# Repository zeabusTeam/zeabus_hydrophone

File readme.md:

## README
This is the version 3 of Zeabus hydrophone system. The system is built around
an FPGA. The system takes the input from 4 hydrophones and performs signal 
conditioning and filtering before sending the outputs to the host computer via 
a USB high-speed connection. The basic specifications of the system are:
- Maximum input frequency is 45 kHz
- Minimum ADC sampling rate is 4.5 mega-sample per second (MSPS)
- Each sample has at least 14-bit resolution
- Utilizes "averaging" sampling mode to down-sampling to the appropriate rate
- Supports variable gain in pre-amplifier unit
- Maximum ADC input voltage is 2 Vp-p
- Supports variable trigger voltage.
- At least 32k samples/channel buffer length
- Perform online FIR filter with user-provided FIR table.
  - FIR filter is an odd-symetric filter (i.e., type1 linear-phase FIR)
  - Each coefficient is 2'complement 32-bit integer

## Concrete specification
ADC: AD9248BSTZ-65 (65 MSPS max)
FPGA: Xilinx Artix 7 XC7A15T (ZTEX FPGA v2.14a)
Clock Buffer: IDT-553S (1:4 Distribute)
OP-AMP: OPA2365 (Dual Op-Amp), OPA365 (Single Op-Amp) [May use -Q1 version for thougher devices]
Digital Potentiometer: MAX5413 (10k), MAX5414 (50k), MAX5415 (100k) (May use MAX5387 as alternative)
ADC Driver: ADA4940-2 to convert single-ended signal to differential signal (Transformer is unsuitable for low freq.)
Voltage Reference: REF1933 (+3.3v and +1.65v outputs are used only for reference. The device requires 5v input)
Capacitors along the signal path should be of C0G type.

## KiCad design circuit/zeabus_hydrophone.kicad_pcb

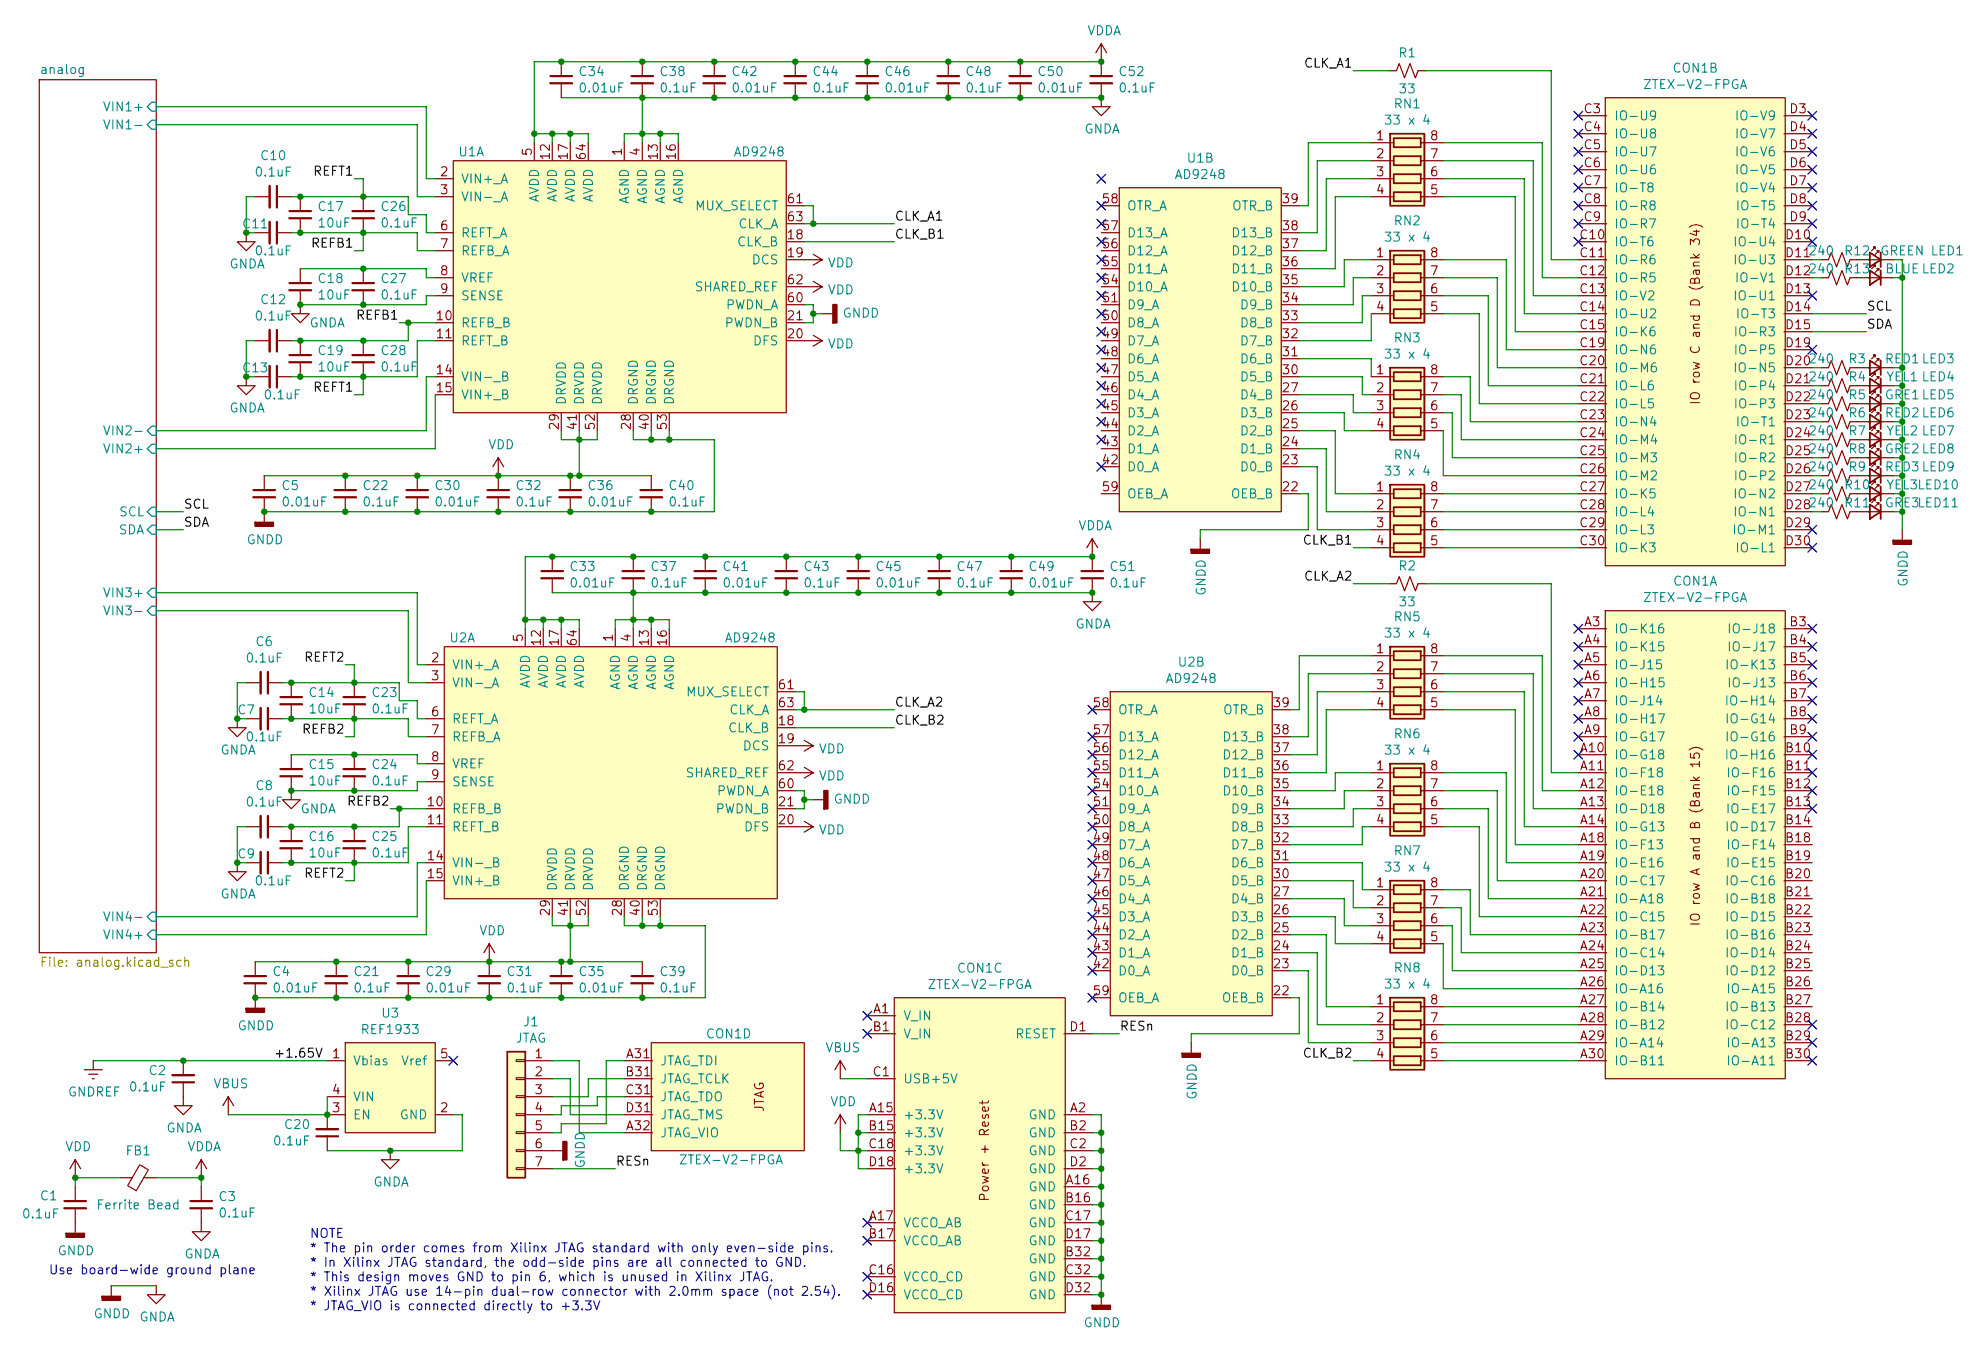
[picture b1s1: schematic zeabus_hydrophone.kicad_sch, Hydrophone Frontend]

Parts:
C1, C2, C3, C6, C7, C8, C9, C10, C11, C12, C13, C20, C21, C22, C23, C24, C25, C26, C27, C28, C31, C32, C37, C38, C39, C40, C43, C44, C47, C48, C51, C52: 0.1uF; C_0603_1608Metric_Pad1.08x0.95mm_HandSolder
C4, C5, C29, C30, C33, C34, C35, C36, C41, C42, C45, C46, C49, C50: 0.01uF; C_0603_1608Metric_Pad1.08x0.95mm_HandSolder
C14, C15, C16, C17, C18, C19: 10uF; C_0805_2012Metric_Pad1.18x1.45mm_HandSolder
CON1: ZTEX-V2-FPGA; ZTEX-V2-FPGA-SMD
FB1: Ferrite Bead; R_0805_2012Metric_Pad1.15x1.40mm_HandSolder
J1: JTAG; PinHeader_1x07_P2.54mm_Vertical
LED1: GREEN; LED_0603_1608Metric_Pad1.05x0.95mm_HandSolder
LED2: BLUE; LED_0603_1608Metric_Pad1.05x0.95mm_HandSolder
LED3: RED1; LED_0603_1608Metric_Pad1.05x0.95mm_HandSolder
LED4: YEL1; LED_0603_1608Metric_Pad1.05x0.95mm_HandSolder
LED5: GRE1; LED_0603_1608Metric_Pad1.05x0.95mm_HandSolder
LED6: RED2; LED_0603_1608Metric_Pad1.05x0.95mm_HandSolder
LED7: YEL2; LED_0603_1608Metric_Pad1.05x0.95mm_HandSolder
LED8: GRE2; LED_0603_1608Metric_Pad1.05x0.95mm_HandSolder
LED9: RED3; LED_0603_1608Metric_Pad1.05x0.95mm_HandSolder
LED10: YEL3; LED_0603_1608Metric_Pad1.05x0.95mm_HandSolder
LED11: GRE3; LED_0603_1608Metric_Pad1.05x0.95mm_HandSolder
R1, R2: 33; R_0603_1608Metric_Pad1.05x0.95mm_HandSolder
R3, R4, R5, R6, R7, R8, R9, R10, R11, R12, R13: 240; R_0603_1608Metric_Pad1.05x0.95mm_HandSolder
RN1, RN2, RN3, RN4, RN5, RN6, RN7, RN8: 33 x 4; R_Array_Convex_4x0603
U1, U2: AD9248; TQFP-64_7x7mm_P0.4mm
U3: REF1933; SOT-23-5

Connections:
/CLK_A1: R1.2, U1.61 (MUX_SELECT), U1.63 (CLK_A)
/CLK_A2: R2.2, U2.61 (MUX_SELECT), U2.63 (CLK_A)
/CLK_B1: RN4.4 (R4.1), U1.18 (CLK_B)
/CLK_B2: RN8.4 (R4.1), U2.18 (CLK_B)
/REFB1: C11.1, C12.1, C17.2, C19.1, C26.2, C28.1, U1.7 (REFB_A), U1.10 (REFB_B)
/REFB2: C7.1, C8.1, C14.2, C16.1, C23.2, C25.1, U2.7 (REFB_A), U2.10 (REFB_B)
/REFT1: C10.1, C13.1, C17.1, C19.2, C26.1, C28.2, U1.6 (REFT_A), U1.11 (REFT_B)
/REFT2: C6.1, C9.1, C14.1, C16.2, C23.1, C25.2, U2.6 (REFT_A), U2.11 (REFT_B)
/RESn: CON1.D1 (RESET), J1.7
/SCL: CON1.D14 (IO-T3); also elsewhere on the board
/SDA: CON1.D15 (IO-R3); also elsewhere on the board
/analog/VIN1+: U1.2 (VIN+_A); also elsewhere on the board
/analog/VIN1-: U1.3 (VIN-_A); also elsewhere on the board
/analog/VIN2+: U1.15 (VIN+_B); also elsewhere on the board
/analog/VIN2-: U1.14 (VIN-_B); also elsewhere on the board
/analog/VIN3+: U2.2 (VIN+_A); also elsewhere on the board
/analog/VIN3-: U2.3 (VIN-_A); also elsewhere on the board
/analog/VIN4+: U2.15 (VIN+_B); also elsewhere on the board
/analog/VIN4-: U2.14 (VIN-_B); also elsewhere on the board
GNDA: C1.2, C2.1, C3.2, C4.2, C5.2, C6.2, C7.2, C8.2, C9.2, C10.2, C11.2, C12.2, C13.2, C15.2, C18.2, C20.1, C21.2, C22.2, C24.2, C27.2, C29.2, C30.2, C31.2, C32.2, C33.2, C34.2, C35.2, C36.2, C37.2, C38.2, C39.2, C40.2, C41.2, C42.2, C43.2, C44.2, C45.2, C46.2, C47.2, C48.2, C49.2, C50.2, C51.2, C52.2, CON1.A2 (GND), CON1.A16 (GND), CON1.B2 (GND), CON1.B16 (GND), CON1.B32 (GND), CON1.C2 (GND), CON1.C17 (GND), CON1.C32 (GND), CON1.D2 (GND), CON1.D17 (GND), CON1.D32 (GND), J1.6, LED1.1 (K), LED2.1 (K), LED3.1 (K), LED4.1 (K), LED5.1 (K), LED6.1 (K), LED7.1 (K), LED8.1 (K), LED9.1 (K), LED10.1 (K), LED11.1 (K), U1.1 (AGND), U1.4 (AGND), U1.9 (SENSE), U1.13 (AGND), U1.16 (AGND), U1.21 (PWDN_B), U1.22 (OEB_B), U1.28 (DRGND), U1.40 (DRGND), U1.53 (DRGND), U1.60 (PWDN_A), U2.1 (AGND), U2.4 (AGND), U2.9 (SENSE), U2.13 (AGND), U2.16 (AGND), U2.21 (PWDN_B), U2.22 (OEB_B), U2.28 (DRGND), U2.40 (DRGND), U2.53 (DRGND), U2.60 (PWDN_A), U3.2 (GND); also elsewhere on the board
GNDREF: C2.2, U3.1 (Vbias); also elsewhere on the board
unnamed: C15.1, C24.1, U2.8 (VREF)
unnamed: C18.1, C27.1, U1.8 (VREF)
unnamed: CON1.A11 (IO-F18), R2.1
unnamed: CON1.A12 (IO-E18), RN5.8 (R1.2)
unnamed: CON1.A13 (IO-D18), RN5.7 (R2.2)
unnamed: CON1.A14 (IO-G13), RN5.6 (R3.2)
unnamed: CON1.A18 (IO-F13), RN5.5 (R4.2)
unnamed: CON1.A19 (IO-E16), RN6.8 (R1.2)
unnamed: CON1.A20 (IO-C17), RN6.7 (R2.2)
unnamed: CON1.A21 (IO-A18), RN6.6 (R3.2)
unnamed: CON1.A22 (IO-C15), RN6.5 (R4.2)
unnamed: CON1.A23 (IO-B17), RN7.8 (R1.2)
unnamed: CON1.A24 (IO-C14), RN7.7 (R2.2)
unnamed: CON1.A25 (IO-D13), RN7.6 (R3.2)
unnamed: CON1.A26 (IO-A16), RN7.5 (R4.2)
unnamed: CON1.A27 (IO-B14), RN8.8 (R1.2)
unnamed: CON1.A28 (IO-B12), RN8.7 (R2.2)
unnamed: CON1.A29 (IO-A14), RN8.6 (R3.2)
unnamed: CON1.A30 (IO-B11), RN8.5 (R4.2)
unnamed: CON1.A31 (JTAG_TDI), J1.5
unnamed: CON1.A32 (JTAG_VIO), J1.1
unnamed: CON1.B31 (JTAG_TCLK), J1.3
unnamed: CON1.C11 (IO-R6), R1.1
unnamed: CON1.C12 (IO-R5), RN1.8 (R1.2)
unnamed: CON1.C13 (IO-V2), RN1.7 (R2.2)
unnamed: CON1.C14 (IO-U2), RN1.6 (R3.2)
unnamed: CON1.C15 (IO-K6), RN1.5 (R4.2)
unnamed: CON1.C19 (IO-N6), RN2.8 (R1.2)
unnamed: CON1.C20 (IO-M6), RN2.7 (R2.2)
unnamed: CON1.C21 (IO-L6), RN2.6 (R3.2)
unnamed: CON1.C22 (IO-L5), RN2.5 (R4.2)
unnamed: CON1.C23 (IO-N4), RN3.8 (R1.2)
unnamed: CON1.C24 (IO-M4), RN3.7 (R2.2)
unnamed: CON1.C25 (IO-M3), RN3.6 (R3.2)
unnamed: CON1.C26 (IO-M2), RN3.5 (R4.2)
unnamed: CON1.C27 (IO-K5), RN4.8 (R1.2)
unnamed: CON1.C28 (IO-L4), RN4.7 (R2.2)
unnamed: CON1.C29 (IO-L3), RN4.6 (R3.2)
unnamed: CON1.C30 (IO-K3), RN4.5 (R4.2)
unnamed: CON1.C31 (JTAG_TDO), J1.4
unnamed: CON1.D11 (IO-U3), R12.1
unnamed: CON1.D12 (IO-V1), R13.1
unnamed: CON1.D20 (IO-N5), R3.2
unnamed: CON1.D21 (IO-P4), R4.2
unnamed: CON1.D22 (IO-P3), R5.2
unnamed: CON1.D23 (IO-T1), R6.2
unnamed: CON1.D24 (IO-R1), R7.2
unnamed: CON1.D25 (IO-R2), R8.2
unnamed: CON1.D26 (IO-P2), R9.2
unnamed: CON1.D27 (IO-N2), R10.2
unnamed: CON1.D28 (IO-N1), R11.2
unnamed: CON1.D31 (JTAG_TMS), J1.2
unnamed: LED1.2 (A), R12.2
unnamed: LED2.2 (A), R13.2
unnamed: LED3.2 (A), R3.1
unnamed: LED4.2 (A), R4.1
unnamed: LED5.2 (A), R5.1
unnamed: LED6.2 (A), R6.1
unnamed: LED7.2 (A), R7.1
unnamed: LED8.2 (A), R8.1
unnamed: LED9.2 (A), R9.1
unnamed: LED10.2 (A), R10.1
unnamed: LED11.2 (A), R11.1
unnamed: RN1.1 (R1.1), U1.39 (OTR_B)
unnamed: RN1.2 (R2.1), U1.38 (D13_B)
unnamed: RN1.3 (R3.1), U1.37 (D12_B)
unnamed: RN1.4 (R4.1), U1.36 (D11_B)
unnamed: RN2.1 (R1.1), U1.35 (D10_B)
unnamed: RN2.2 (R2.1), U1.34 (D9_B)
unnamed: RN2.3 (R3.1), U1.33 (D8_B)
unnamed: RN2.4 (R4.1), U1.32 (D7_B)
unnamed: RN3.1 (R1.1), U1.31 (D6_B)
unnamed: RN3.2 (R2.1), U1.30 (D5_B)
unnamed: RN3.3 (R3.1), U1.27 (D4_B)
unnamed: RN3.4 (R4.1), U1.26 (D3_B)
unnamed: RN4.1 (R1.1), U1.25 (D2_B)
unnamed: RN4.2 (R2.1), U1.24 (D1_B)
unnamed: RN4.3 (R3.1), U1.23 (D0_B)
unnamed: RN5.1 (R1.1), U2.39 (OTR_B)
unnamed: RN5.2 (R2.1), U2.38 (D13_B)
unnamed: RN5.3 (R3.1), U2.37 (D12_B)
unnamed: RN5.4 (R4.1), U2.36 (D11_B)
unnamed: RN6.1 (R1.1), U2.35 (D10_B)
unnamed: RN6.2 (R2.1), U2.34 (D9_B)
unnamed: RN6.3 (R3.1), U2.33 (D8_B)
unnamed: RN6.4 (R4.1), U2.32 (D7_B)
unnamed: RN7.1 (R1.1), U2.31 (D6_B)
unnamed: RN7.2 (R2.1), U2.30 (D5_B)
unnamed: RN7.3 (R3.1), U2.27 (D4_B)
unnamed: RN7.4 (R4.1), U2.26 (D3_B)
unnamed: RN8.1 (R1.1), U2.25 (D2_B)
unnamed: RN8.2 (R2.1), U2.24 (D1_B)
unnamed: RN8.3 (R3.1), U2.23 (D0_B)
VBUS: C20.2, CON1.C1 (USB+5V), U3.3 (EN), U3.4 (VIN)
VDD: C1.1, C4.1, C5.1, C21.1, C22.1, C29.1, C30.1, C31.1, C32.1, C35.1, C36.1, C39.1, C40.1, CON1.A15 (+3.3V), CON1.B15 (+3.3V), CON1.C18 (+3.3V), CON1.D18 (+3.3V), FB1.1, U1.19 (DCS), U1.20 (DFS), U1.29 (DRVDD), U1.41 (DRVDD), U1.52 (DRVDD), U1.62 (SHARED_REF), U2.19 (DCS), U2.20 (DFS), U2.29 (DRVDD), U2.41 (DRVDD), U2.52 (DRVDD), U2.62 (SHARED_REF); also elsewhere on the board
VDDA: C3.1, C33.1, C34.1, C37.1, C38.1, C41.1, C42.1, C43.1, C44.1, C45.1, C46.1, C47.1, C48.1, C49.1, C50.1, C51.1, C52.1, FB1.2, U1.5 (AVDD), U1.12 (AVDD), U1.17 (AVDD), U1.64 (AVDD), U2.5 (AVDD), U2.12 (AVDD), U2.17 (AVDD), U2.64 (AVDD); also elsewhere on the board

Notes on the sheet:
Use board-wide ground plane
NOTE * The pin order comes from Xilinx JTAG standard with only even-side pins. * In Xilinx JTAG standard, the odd-side pins are all connected to GND. * This design moves GND to pin 6, which is unused in Xilinx JTAG. * Xilinx JTAG use 14-pin dual-row connector with 2.0mm space (not 2.54). * JTAG_VIO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

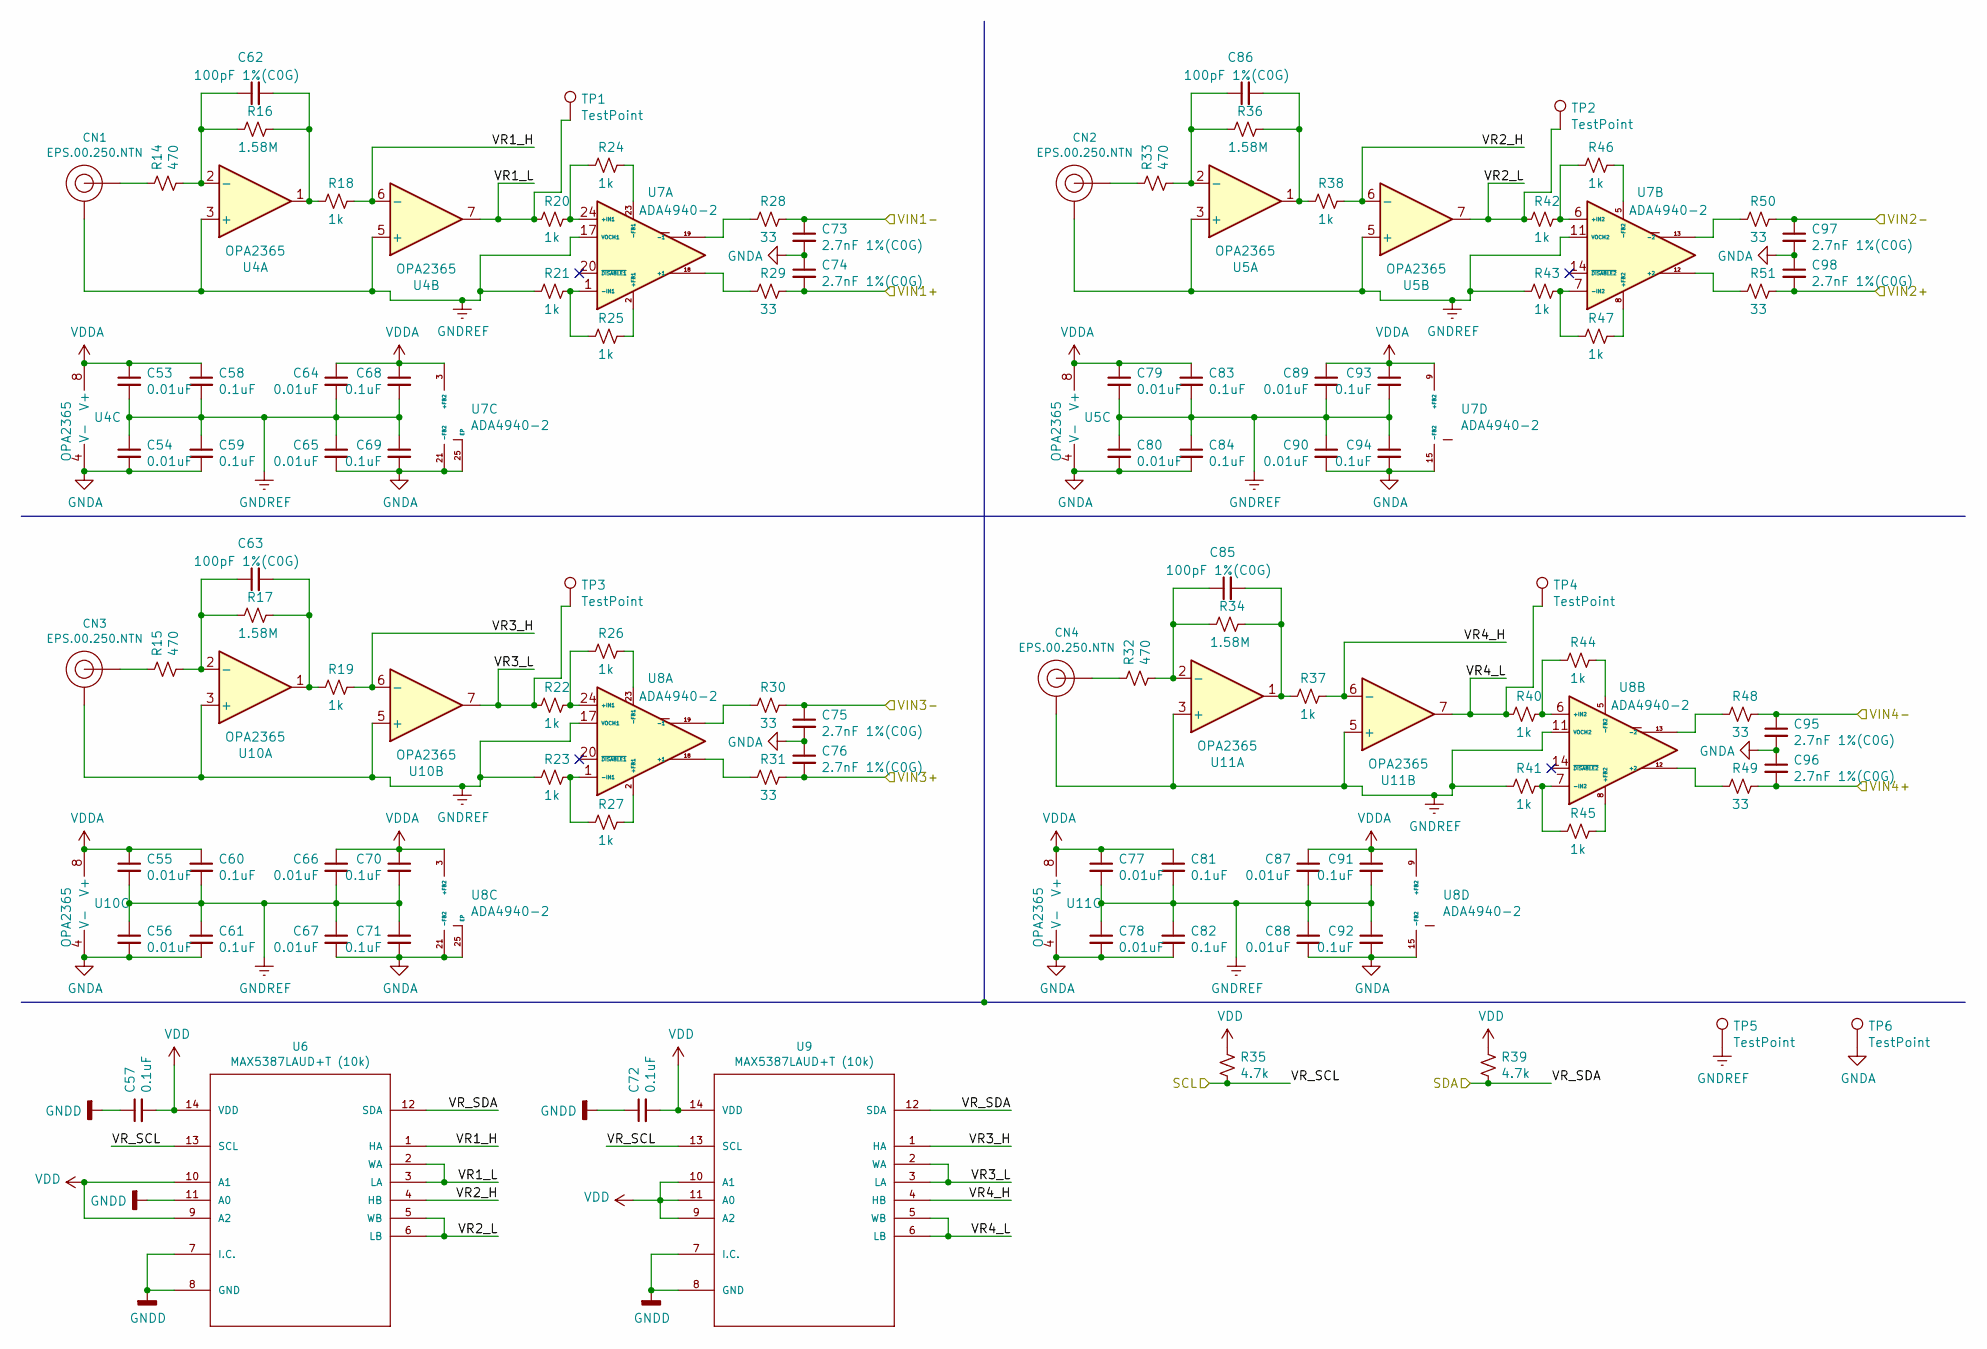
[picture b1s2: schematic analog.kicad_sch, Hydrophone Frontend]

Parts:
C53, C54, C55, C56, C64, C65, C66, C67, C77, C78, C79, C80, C87, C88, C89, C90: 0.01uF; C_0603_1608Metric_Pad1.08x0.95mm_HandSolder
C57, C58, C59, C60, C61, C68, C69, C70, C71, C72, C81, C82, C83, C84, C91, C92, C93, C94: 0.1uF; C_0603_1608Metric_Pad1.08x0.95mm_HandSolder
C62, C63, C85, C86: 100pF 1%(C0G); C_0603_1608Metric_Pad1.08x0.95mm_HandSolder
C73, C74, C75, C76, C95, C96, C97, C98: 2.7nF 1%(C0G); C_0603_1608Metric_Pad1.08x0.95mm_HandSolder
CN1, CN2, CN3, CN4: EPS.00.250.NTN; EPS-00-250
R14, R15, R32, R33: 470; R_0603_1608Metric_Pad1.05x0.95mm_HandSolder
R16, R17, R34, R36: 1.58M; R_0603_1608Metric_Pad1.05x0.95mm_HandSolder
R18, R19, R20, R21, R22, R23, R24, R25, R26, R27, R37, R38, R40, R41, R42, R43, R44, R45, R46, R47: 1k; R_0603_1608Metric_Pad1.05x0.95mm_HandSolder
R28, R29, R30, R31, R48, R49, R50, R51: 33; R_0603_1608Metric_Pad1.05x0.95mm_HandSolder
R35, R39: 4.7k; R_0603_1608Metric_Pad1.05x0.95mm_HandSolder
TP1, TP2, TP3, TP4, TP5, TP6: TestPoint; PinSocket_1x01_P2.54mm_Vertical
U4, U5, U10, U11: OPA2365; SOIC-8_3.9x4.9mm_P1.27mm
U6, U9: MAX5387LAUD+T (10k); TSSOP-14_4.4x5mm_P0.65mm
U7, U8: ADA4940-2; LFCSP-24-1EP_4x4mm_P0.5mm_EP2.5x2.5mm

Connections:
/SCL: R35.2, U6.13 (SCL), U9.13 (SCL); also elsewhere on the board
/SDA: R39.2, U6.12 (SDA), U9.12 (SDA); also elsewhere on the board
/analog/VIN1+: C74.2, R29.1; also elsewhere on the board
/analog/VIN1-: C73.1, R28.1; also elsewhere on the board
/analog/VIN2+: C98.2, R51.1; also elsewhere on the board
/analog/VIN2-: C97.1, R50.1; also elsewhere on the board
/analog/VIN3+: C76.2, R31.1; also elsewhere on the board
/analog/VIN3-: C75.1, R30.1; also elsewhere on the board
/analog/VIN4+: C96.2, R49.1; also elsewhere on the board
/analog/VIN4-: C95.1, R48.1; also elsewhere on the board
/analog/VR1_H: R18.1, U4.6 (-), U6.1 (HA)
/analog/VR1_L: R20.2, TP1.1, U4.7, U6.2 (WA), U6.3 (LA)
/analog/VR2_H: R38.1, U5.6 (-), U6.4 (HB)
/analog/VR2_L: R42.2, TP2.1, U5.7, U6.5 (WB), U6.6 (LB)
/analog/VR3_H: R19.1, U9.1 (HA), U10.6 (-)
/analog/VR3_L: R22.2, TP3.1, U9.2 (WA), U9.3 (LA), U10.7
/analog/VR4_H: R37.1, U9.4 (HB), U11.6 (-)
/analog/VR4_L: R40.2, TP4.1, U9.5 (WB), U9.6 (LB), U11.7
GNDA: C54.2, C56.2, C57.1, C59.2, C61.2, C65.2, C67.2, C69.2, C71.2, C72.1, C73.2, C74.1, C75.2, C76.1, C78.2, C80.2, C82.2, C84.2, C88.2, C90.2, C92.2, C94.2, C95.2, C96.1, C97.2, C98.1, TP6.1, U4.4 (V-), U5.4 (V-), U6.7 (I.C.), U6.8 (GND), U6.11 (A0), U7.15 (-FB2), U7.16 (-FB2), U7.21 (-FB2), U7.22 (-FB2), U7.25 (EP), U8.15 (-FB2), U8.16 (-FB2), U8.21 (-FB2), U8.22 (-FB2), U8.25 (EP), U9.7 (I.C.), U9.8 (GND), U10.4 (V-), U11.4 (V-); also elsewhere on the board
GNDREF: C53.2, C54.1, C55.2, C56.1, C58.2, C59.1, C60.2, C61.1, C64.2, C65.1, C66.2, C67.1, C68.2, C69.1, C70.2, C71.1, C77.2, C78.1, C79.2, C80.1, C81.2, C82.1, C83.2, C84.1, C87.2, C88.1, C89.2, C90.1, C91.2, C92.1, C93.2, C94.1, CN1.2 (GND), CN1.3 (GND), CN1.4 (GND), CN1.5 (GND), CN2.2 (GND), CN2.3 (GND), CN2.4 (GND), CN2.5 (GND), CN3.2 (GND), CN3.3 (GND), CN3.4 (GND), CN3.5 (GND), CN4.2 (GND), CN4.3 (GND), CN4.4 (GND), CN4.5 (GND), R21.2, R23.2, R41.2, R43.2, TP5.1, U4.3 (+), U4.5 (+), U5.3 (+), U5.5 (+), U7.11 (VOCM2), U7.17 (VOCM1), U8.11 (VOCM2), U8.17 (VOCM1), U10.3 (+), U10.5 (+), U11.3 (+), U11.5 (+); also elsewhere on the board
unnamed: C62.1, R14.2, R16.2, U4.2 (-)
unnamed: C62.2, R16.1, R18.2, U4.1
unnamed: C63.1, R15.2, R17.2, U10.2 (-)
unnamed: C63.2, R17.1, R19.2, U10.1
unnamed: C85.1, R32.2, R34.2, U11.2 (-)
unnamed: C85.2, R34.1, R37.2, U11.1
unnamed: C86.1, R33.2, R36.2, U5.2 (-)
unnamed: C86.2, R36.1, R38.2, U5.1
unnamed: CN1.1 (OUT), R14.1
unnamed: CN2.1 (OUT), R33.1
unnamed: CN3.1 (OUT), R15.1
unnamed: CN4.1 (OUT), R32.1
unnamed: R20.1, R24.2, U7.24 (+IN1)
unnamed: R21.1, R25.2, U7.1 (-IN1)
unnamed: R22.1, R26.2, U8.24 (+IN1)
unnamed: R23.1, R27.2, U8.1 (-IN1)
unnamed: R24.1, U7.23 (-FB1)
unnamed: R25.1, U7.2 (+FB1)
unnamed: R26.1, U8.23 (-FB1)
unnamed: R27.1, U8.2 (+FB1)
unnamed: R28.2, U7.19 (-1)
unnamed: R29.2, U7.18 (+1)
unnamed: R30.2, U8.19 (-1)
unnamed: R31.2, U8.18 (+1)
unnamed: R40.1, R44.2, U8.6 (+IN2)
unnamed: R41.1, R45.2, U8.7 (-IN2)
unnamed: R42.1, R46.2, U7.6 (+IN2)
unnamed: R43.1, R47.2, U7.7 (-IN2)
unnamed: R44.1, U8.5 (-FB2)
unnamed: R45.1, U8.8 (+FB2)
unnamed: R46.1, U7.5 (-FB2)
unnamed: R47.1, U7.8 (+FB2)
unnamed: R48.2, U8.13 (-2)
unnamed: R49.2, U8.12 (+2)
unnamed: R50.2, U7.13 (-2)
unnamed: R51.2, U7.12 (+2)
VDD: C57.2, C72.2, R35.1, R39.1, U6.9 (A2), U6.10 (A1), U6.14 (VDD), U9.9 (A2), U9.10 (A1), U9.11 (A0), U9.14 (VDD); also elsewhere on the board
VDDA: C53.1, C55.1, C58.1, C60.1, C64.1, C66.1, C68.1, C70.1, C77.1, C79.1, C81.1, C83.1, C87.1, C89.1, C91.1, C93.1, U4.8 (V+), U5.8 (V+), U7.3 (+FB2), U7.4 (+FB2), U7.9 (+FB2), U7.10 (+FB2), U8.3 (+FB2), U8.4 (+FB2), U8.9 (+FB2), U8.10 (+FB2), U10.8 (V+), U11.8 (V+); also elsewhere on the board

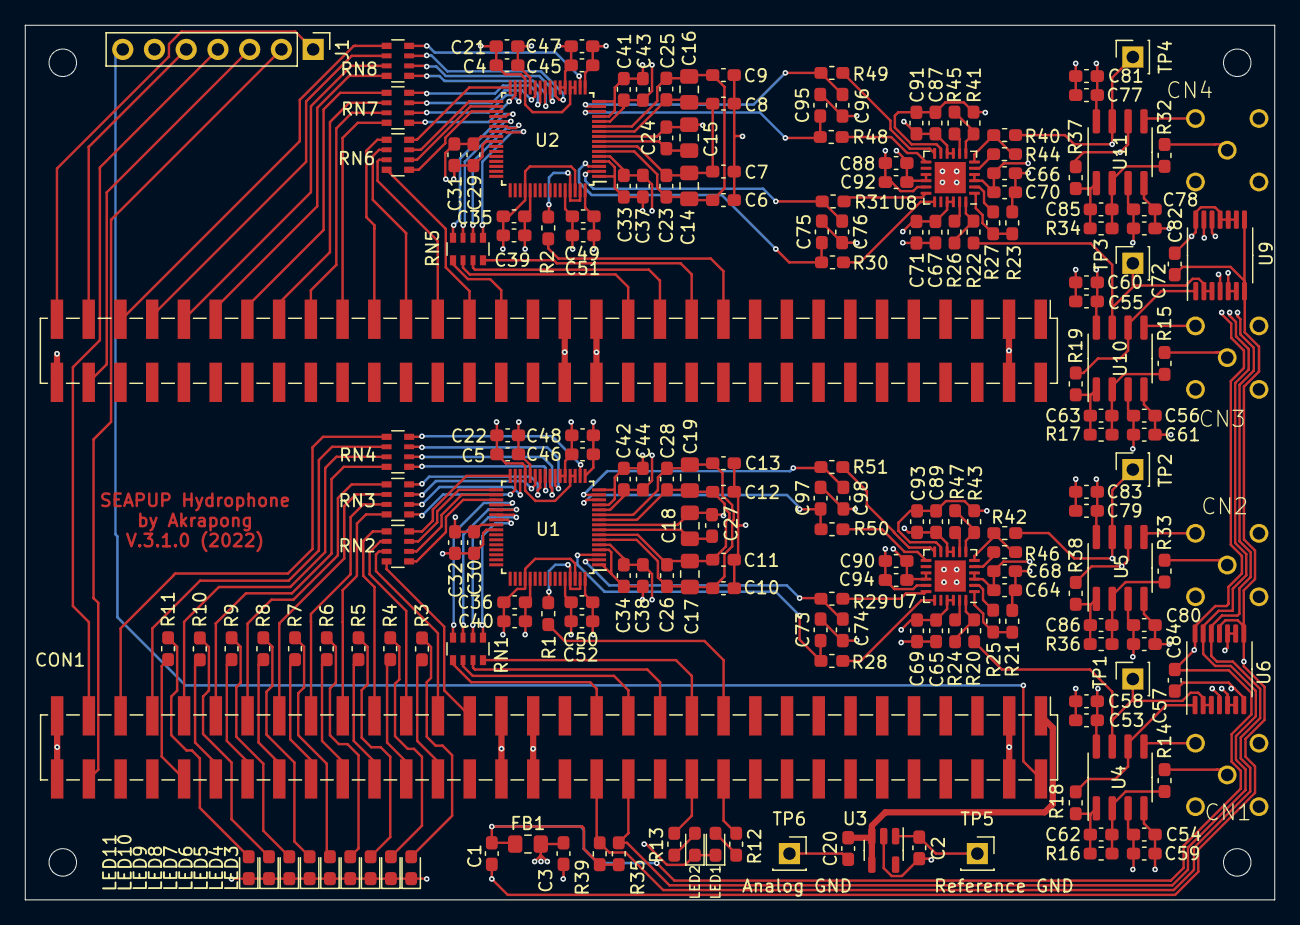
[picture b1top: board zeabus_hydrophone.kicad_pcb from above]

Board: 4 copper layers, 100.0 x 70.0 mm, 192 parts (0 on the bottom side), 161 nets.

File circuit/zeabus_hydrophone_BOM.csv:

Ref,Qnty,Value,Footprint
,,,
"C1, C2, C3, C6, C7, C8, C9, C10, C11, C12, C13, C20, C21, C22, C23, C24, C25, C26, C27, C28, C31, C32, C37, C38, C39, C40, C43, C44, C47, C48, C51, C52, C57, C58, C59, C60, C61, C68, C69, C70, C71, C72, C81, C82, C83, C84, C91, C92, C93, C94, ",50,0.1uF,Capacitor_SMD:C_0603_1608Metric_Pad1.08x0.95mm_HandSolder
,,,
"C4, C5, C29, C30, C33, C34, C35, C36, C41, C42, C45, C46, C49, C50, C53, C54, C55, C56, C64, C65, C66, C67, C77, C78, C79, C80, C87, C88, C89, C90, ",30,0.01uF,Capacitor_SMD:C_0603_1608Metric_Pad1.08x0.95mm_HandSolder
,,,
"C14, C15, C16, C17, C18, C19, ",6,10uF,Capacitor_SMD:C_0805_2012Metric_Pad1.18x1.45mm_HandSolder
,,,
"C62, C63, C85, C86, ",4,100pF 1%(C0G),Capacitor_SMD:C_0603_1608Metric_Pad1.08x0.95mm_HandSolder
,,,
"C73, C74, C75, C76, C95, C96, C97, C98, ",8,2.7nF 1%(C0G),Capacitor_SMD:C_0603_1608Metric_Pad1.08x0.95mm_HandSolder
,,,
"CN1, CN2, CN3, CN4, ",4,EPS.00.250.NTN,zeabus:EPS-00-250
,,,
"CON1, ",1,ZTEX-V2-FPGA,zeabus:ZTEX-V2-FPGA-SMD
,,,
"FB1, ",1,Ferrite Bead,Resistor_SMD:R_0805_2012Metric_Pad1.15x1.40mm_HandSolder
,,,
"J1, ",1,JTAG,Connector_PinHeader_2.54mm:PinHeader_1x07_P2.54mm_Vertical
,,,
"LED1, LED5, LED8, LED11",1,GREEN,LED_SMD:LED_0603_1608Metric_Pad1.05x0.95mm_HandSolder
,,,
"LED2, ",1,BLUE,LED_SMD:LED_0603_1608Metric_Pad1.05x0.95mm_HandSolder
,,,
"LED3, LED6, LED9",1,RED,LED_SMD:LED_0603_1608Metric_Pad1.05x0.95mm_HandSolder
,,,
"LED4, LED7, LED10",1,YELLLOW,LED_SMD:LED_0603_1608Metric_Pad1.05x0.95mm_HandSolder
,,,
"R1, R2, R28, R29, R30, R31, R48, R49, R50, R51, ",10,33,Resistor_SMD:R_0603_1608Metric_Pad1.05x0.95mm_HandSolder
,,,
"R3, R4, R5, R6, R7, R8, R9, R10, R11, R12, R13, ",11,240,Resistor_SMD:R_0603_1608Metric_Pad1.05x0.95mm_HandSolder
,,,
"R14, R15, R32, R33, ",4,470,Resistor_SMD:R_0603_1608Metric_Pad1.05x0.95mm_HandSolder
,,,
"R16, R17, R34, R36, ",4,1.58M,Resistor_SMD:R_0603_1608Metric_Pad1.05x0.95mm_HandSolder
,,,
"R18, R19, R20, R21, R22, R23, R24, R25, R26, R27, R37, R38, R40, R41, R42, R43, R44, R45, R46, R47, ",20,1k,Resistor_SMD:R_0603_1608Metric_Pad1.05x0.95mm_HandSolder
,,,
"R35, R39, ",2,4.7k,Resistor_SMD:R_0603_1608Metric_Pad1.05x0.95mm_HandSolder
,,,
"RN1, RN2, RN3, RN4, RN5, RN6, RN7, RN8, ",8,33 x 4,Resistor_SMD:R_Array_Convex_4x0603
,,,
"TP1, TP2, TP3, TP4, TP5, TP6, ",6,TestPoint,Connector_PinSocket_2.54mm:PinSocket_1x01_P2.54mm_Vertical
,,,
"U1, U2, ",2,AD9248,Package_QFP:TQFP-64_7x7mm_P0.4mm
,,,
"U3, ",1,REF1933,Package_TO_SOT_SMD:SOT-23-5
,,,
"U4, U5, U10, U11, ",4,OPA2365,Package_SO:SOIC-8_3.9x4.9mm_P1.27mm
,,,
"U6, U9, ",2,MAX5387LAUD+T (10k),Package_SO:TSSOP-14_4.4x5mm_P0.65mm
,,,
"U7, U8, ",2,ADA4940-2,Package_CSP:LFCSP-24-1EP_4x4mm_P0.5mm_EP2.5x2.5mm

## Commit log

2018-05-28 finish adc with dma
2018-05-28 Add Datasheet
2018-06-01 set I2C , CDC USB
2018-06-02 Detect pulse form hydrophone
2018-06-02 rewrite code and add comment
2018-06-03 finish Get_Frame_Handler
2018-06-12 add CMSIS DSP LIB
2018-06-13 add Get Freq
2018-06-14 Add Down Sampling Function
2018-06-14 commit before generate code form STM32CUBEMX
2018-06-14 add Demod function and Change timer2 to tick at 200kHz
2018-06-16 add lowpass filter after signal demod
2018-06-16 Set UART global interupt
2018-06-16 UART TX and RX simple interrupt
2018-06-19 finish debug Get_frame_handler and add Wait_DMA function
2018-06-20 Debug Get_frame_handler
2018-06-20 abs_thres_cfar added
2018-06-23 set freq using python
2018-07-06 debug freq
2018-07-10 add pulse_detect function
2018-07-10 fix warning bug
2018-07-10 edit uart transmit function
2018-07-11 sent signal using USB comm
2018-07-14 change front-theshold to CFAR algo
2018-07-14 change front-theshold to CFAR algo and debug
2018-07-14 init branch CFAR
2018-07-14 sent data to python after pulse detect (100 sample)
2018-07-14 py data ready to process N add ex py code
2018-07-15 change adc sampling rate to 191.93kHz
2018-07-15 debug fft function
2018-07-15 can set parameter form python
2018-07-15 add hydrophone_arrangement function
2018-07-15 python save and load sample to file
2018-07-16 add bearing estimator python code
2018-07-27 debug uart tx
2018-07-30 init branch
2018-07-30 finish code on dsp board and rewrite python code
2018-07-31 connect to ROS
2019-03-05 Release for SAUVC2019
2019-06-12 Change Set_LNA_Gain to work with the frontend version 2
2019-07-13 Optimize DSP board firmware plus some clean up in hydrophone_serial.py
2019-07-15 Convert python code into ROS node. The result is not tested yet.
2019-07-15 Rename app module to make name clearer
2019-07-16 Release 2.0.0 - Bug fixed - Add frequency boundaries
    ** This commit should be considered as Release 2.0.0
2019-07-20 made the python directory into ros package
2019-07-20 added .gitignore
2019-07-20 made zeabus_hydrophone into usable package
2019-07-20 added Shebang to hydrophone_ros_node.py
2019-07-20 fixed init_node parameter and rospy.logerror to rospy.logerr
2019-07-20 imported services in hydrophone_ros_node.py
2019-07-20 changed topic of services in hydrophone_ros_node.py
2019-07-20 fixed target of the thread and the node will exit on hydrophone not found
2019-07-20 could launch the node from launch files
2019-07-20 fixed param of launch files in the package
2019-07-22 - Added ADC_MASK in common.h to reduce ADC resolution - Reduced PULSE_HEADER_SIZE in common.h from 1200 to 1000 - Fixed some bugs in ads_threshold.c - Fixed ADC value normalization bug and convert th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
2019-07-22 Fixed hydrophone initial configuration bug in __main__
2019-07-22 - Change the firmware to send out the detected signal even its frequency is unmatched. - Add function to python code to support frequency-unmatched signal - Remove all code related to graph plotting
2019-07-22 Minor commit
2019-07-24 Fixed ADC offset value (expected 1.65V but measured at about 1.5V)
2019-09-30 Finalized the current work in version 2. It does not work well because of high noise and low sampling rate.
2019-10-20 Describe key specifications and chosen parts.
2019-10-28 Add Xilinx and ZTEX USB 2.14 data
2019-11-27 Finish the hardware schematic. Ready for PCB and programming.
2019-11-29 Finish schematic and footprint assignment. Ready for PCB
2019-12-03 Starting of firmware development. PCB is yet to route.
2019-12-09 Some firmware files added
2019-12-10 Finish PCB Layout. Change FPGA pins for easier PCB routing.
2019-12-15 Finish PCB routing. Some device drivers in firmware are tested
2019-12-21 Basic firmware done. Wait for FX3S->FPGA part
2019-12-29 Finish Trigger logic design and test-bench
2019-12-29 Update C10uF footprint from 0603 to 0805 and add BOM
2019-12-29 Fix EOL consistency
2019-12-29 Change all EOL character from CRLF to LF
2019-12-29 Add Vivado cache to .gitignore
2019-12-29 Attempt to fix inconsistency between Mac and Windows
2020-01-03 Add green and blue LEDs. Update gerber file.
2020-01-04 Complete BOM
2020-01-07 Finish SlaveFIFO interface
2020-01-17 Finish Average64 Filter and Median Filter. All major parts except FIR are done
2020-01-27 Re-write FPGA code for Slave FIFO used to communicate with FX3S
2020-02-04 Add I2C to FPGA firmware and re-organized modules to decoupling each channel. Also add slave FIFO functions to FX3S firmware.
2020-02-09 Reorganized PCB layout to minimize difference between ADC data trace lengths. Also finished all elements of FPGA verilog files. The next FPGA coding is the top module.
2020-02-17 Correction all FPGA modules to realize into actual chip. Also generated the .BIT file.
2020-02-22 Increase stack size of the main task of FX3S firmware. Fixed some bugs in FX3S firmware. Started some parts of python code.
2020-02-25 Fixed some USB bugs. Add SlaveFIFO verification code
2020-02-25 Update .gitignre to bypass cache files
2020-02-27 Fixed bug in Slave FIFO in both Verilog and FX3S firmware. The FX3S part should be ready for production.
2020-02-27 Remove automatic releasing soft-reset after SlaveFIFO starting. Now the soft-reset may be armed automatically but must be released manually.
2020-03-03 Add packet-header generator to FPGA. Add support for FIR-filter control signal in FX3S (FPGA will support soon)
2020-03-03 Fixed bug for new FIR enable command in FX3S firmware
2020-03-18 First passing the test system. All timings are consistent.
2020-03-25 Pass basic verification for data acquisition. Next step is to verify configuration-setting functions
2020-04-20 Add IQ demodulation and Biquad low-pass filter
2020-04-21 Add IQ demod and Biquad filter plus some python code
2021-12-14 Prepare for Robosub 2022
2021-12-15 Update pdf
2021-12-15 minor doc correction
2022-02-15 New version
    This is the first commit that pass all simulation and ready for real test
2022-02-23 Finish Verilog revision and correct most file errors
2022-02-26 Re-arrange and re-route PCB with some correction
2022-03-03 Change FPGA-board socket from THT to SMD
2022-03-03 Change mounting holes to m2-screws
2022-03-15 Finalized 2022 design with all gerber and bom
2022-04-13 Finalized but not yet synthesized
2022-04-14 Finished and Generated bitstream
2022-04-26 Modified packetizer to cap max packet size
2022-06-01 Sync commit to GitLab current
2022-06-15 Migrate all changes from GitLab
2022-06-15 remove .gitattribute
2022-06-15 Commit all changes
